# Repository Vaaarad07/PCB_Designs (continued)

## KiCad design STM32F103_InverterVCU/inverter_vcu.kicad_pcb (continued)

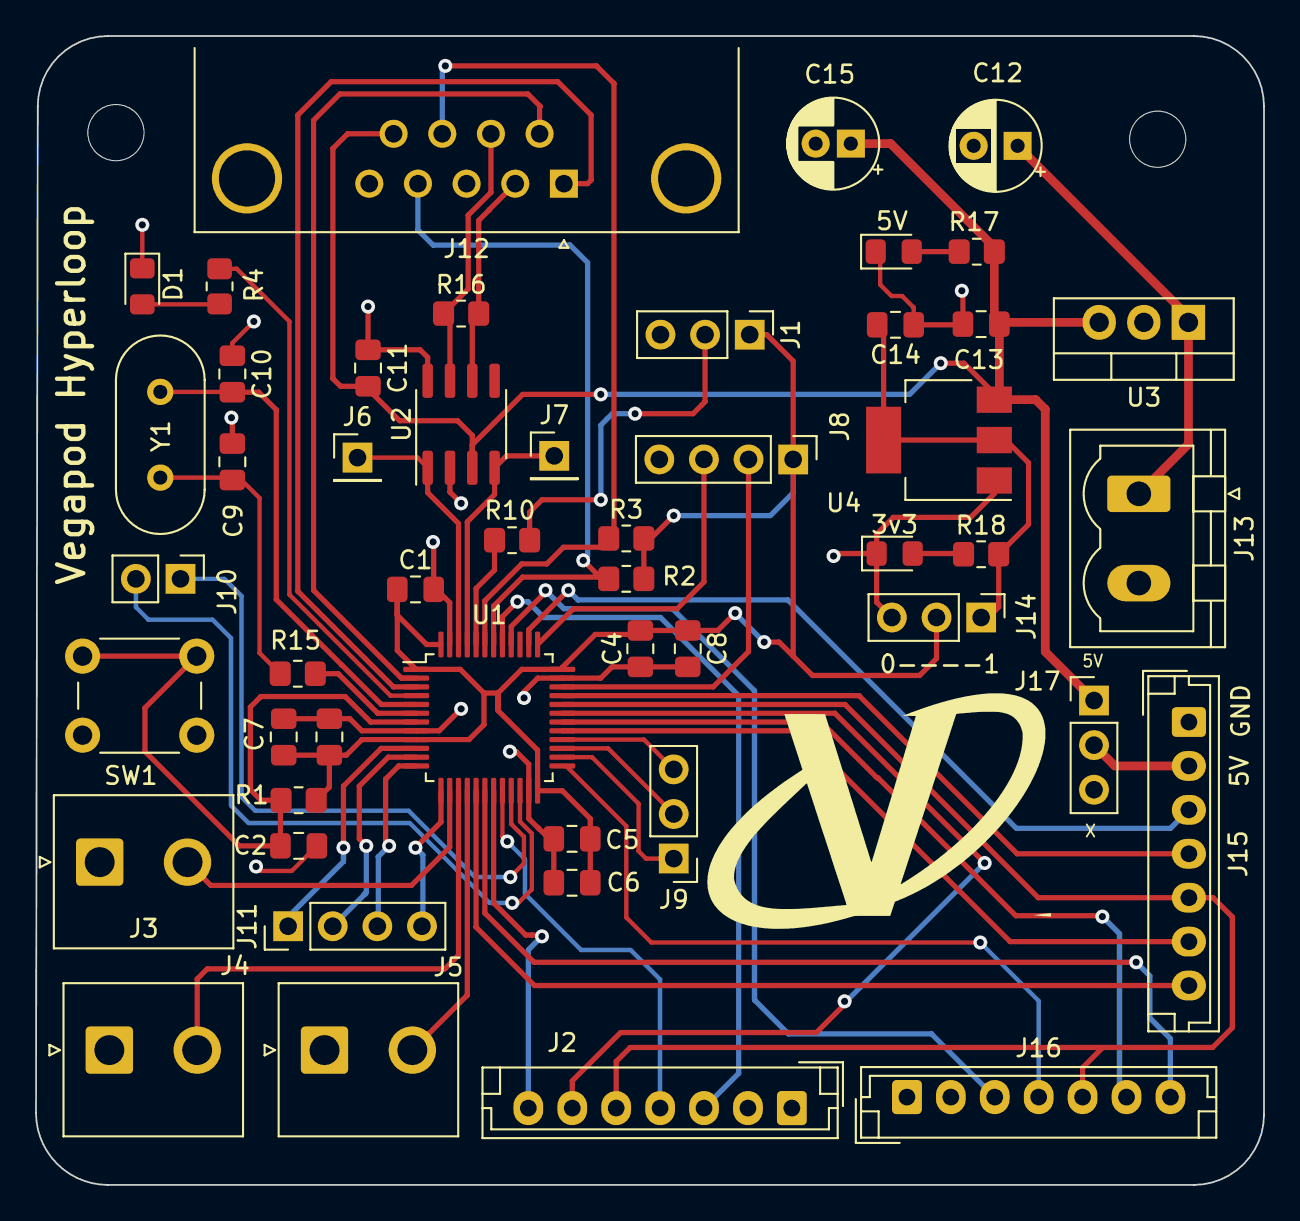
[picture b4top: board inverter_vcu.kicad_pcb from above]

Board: 2 copper layers, 69.9 x 65.4 mm, 50 parts (0 on the bottom side), 51 nets.

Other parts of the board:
3v3, 5V: LED; LED_0805_2012Metric_Pad1.15x1.40mm_HandSolder

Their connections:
GND: 3v3.1 (K), 5V.1 (K); also elsewhere on the board
unnamed 47: 5V.2 (A); also elsewhere on the board
unnamed 48: 3v3.2 (A); also elsewhere on the board

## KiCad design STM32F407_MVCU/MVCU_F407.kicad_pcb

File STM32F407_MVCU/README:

This folder contains KiCad PCB files for a custom Board.

This is a 4 layer STM32F407VGT6 custom board used as a MVCU in a vehicle control application.
The board connects to 5 separate Vehicle control units through DB9 connectors over the CAN bus. 
Following are some of the features of the board -
	Main input range 9-36 volts. Two power regulators to have two separate buses of 5V and 3.3V respectively.
	5 DB9 ports for VCU connections over CAN bus along with reserved gpios.
	RF transceiver (Xbee S2C pro)
	7 segment display
	DB9 port for IMU (Pollux 2) with RS232 to serial converter 
	SD Card slot
	10 User LEDs 
	5-pin Debugger/programmer connector
	Current monitoring
	UART, SPI, ADC, DAC, I2C connections

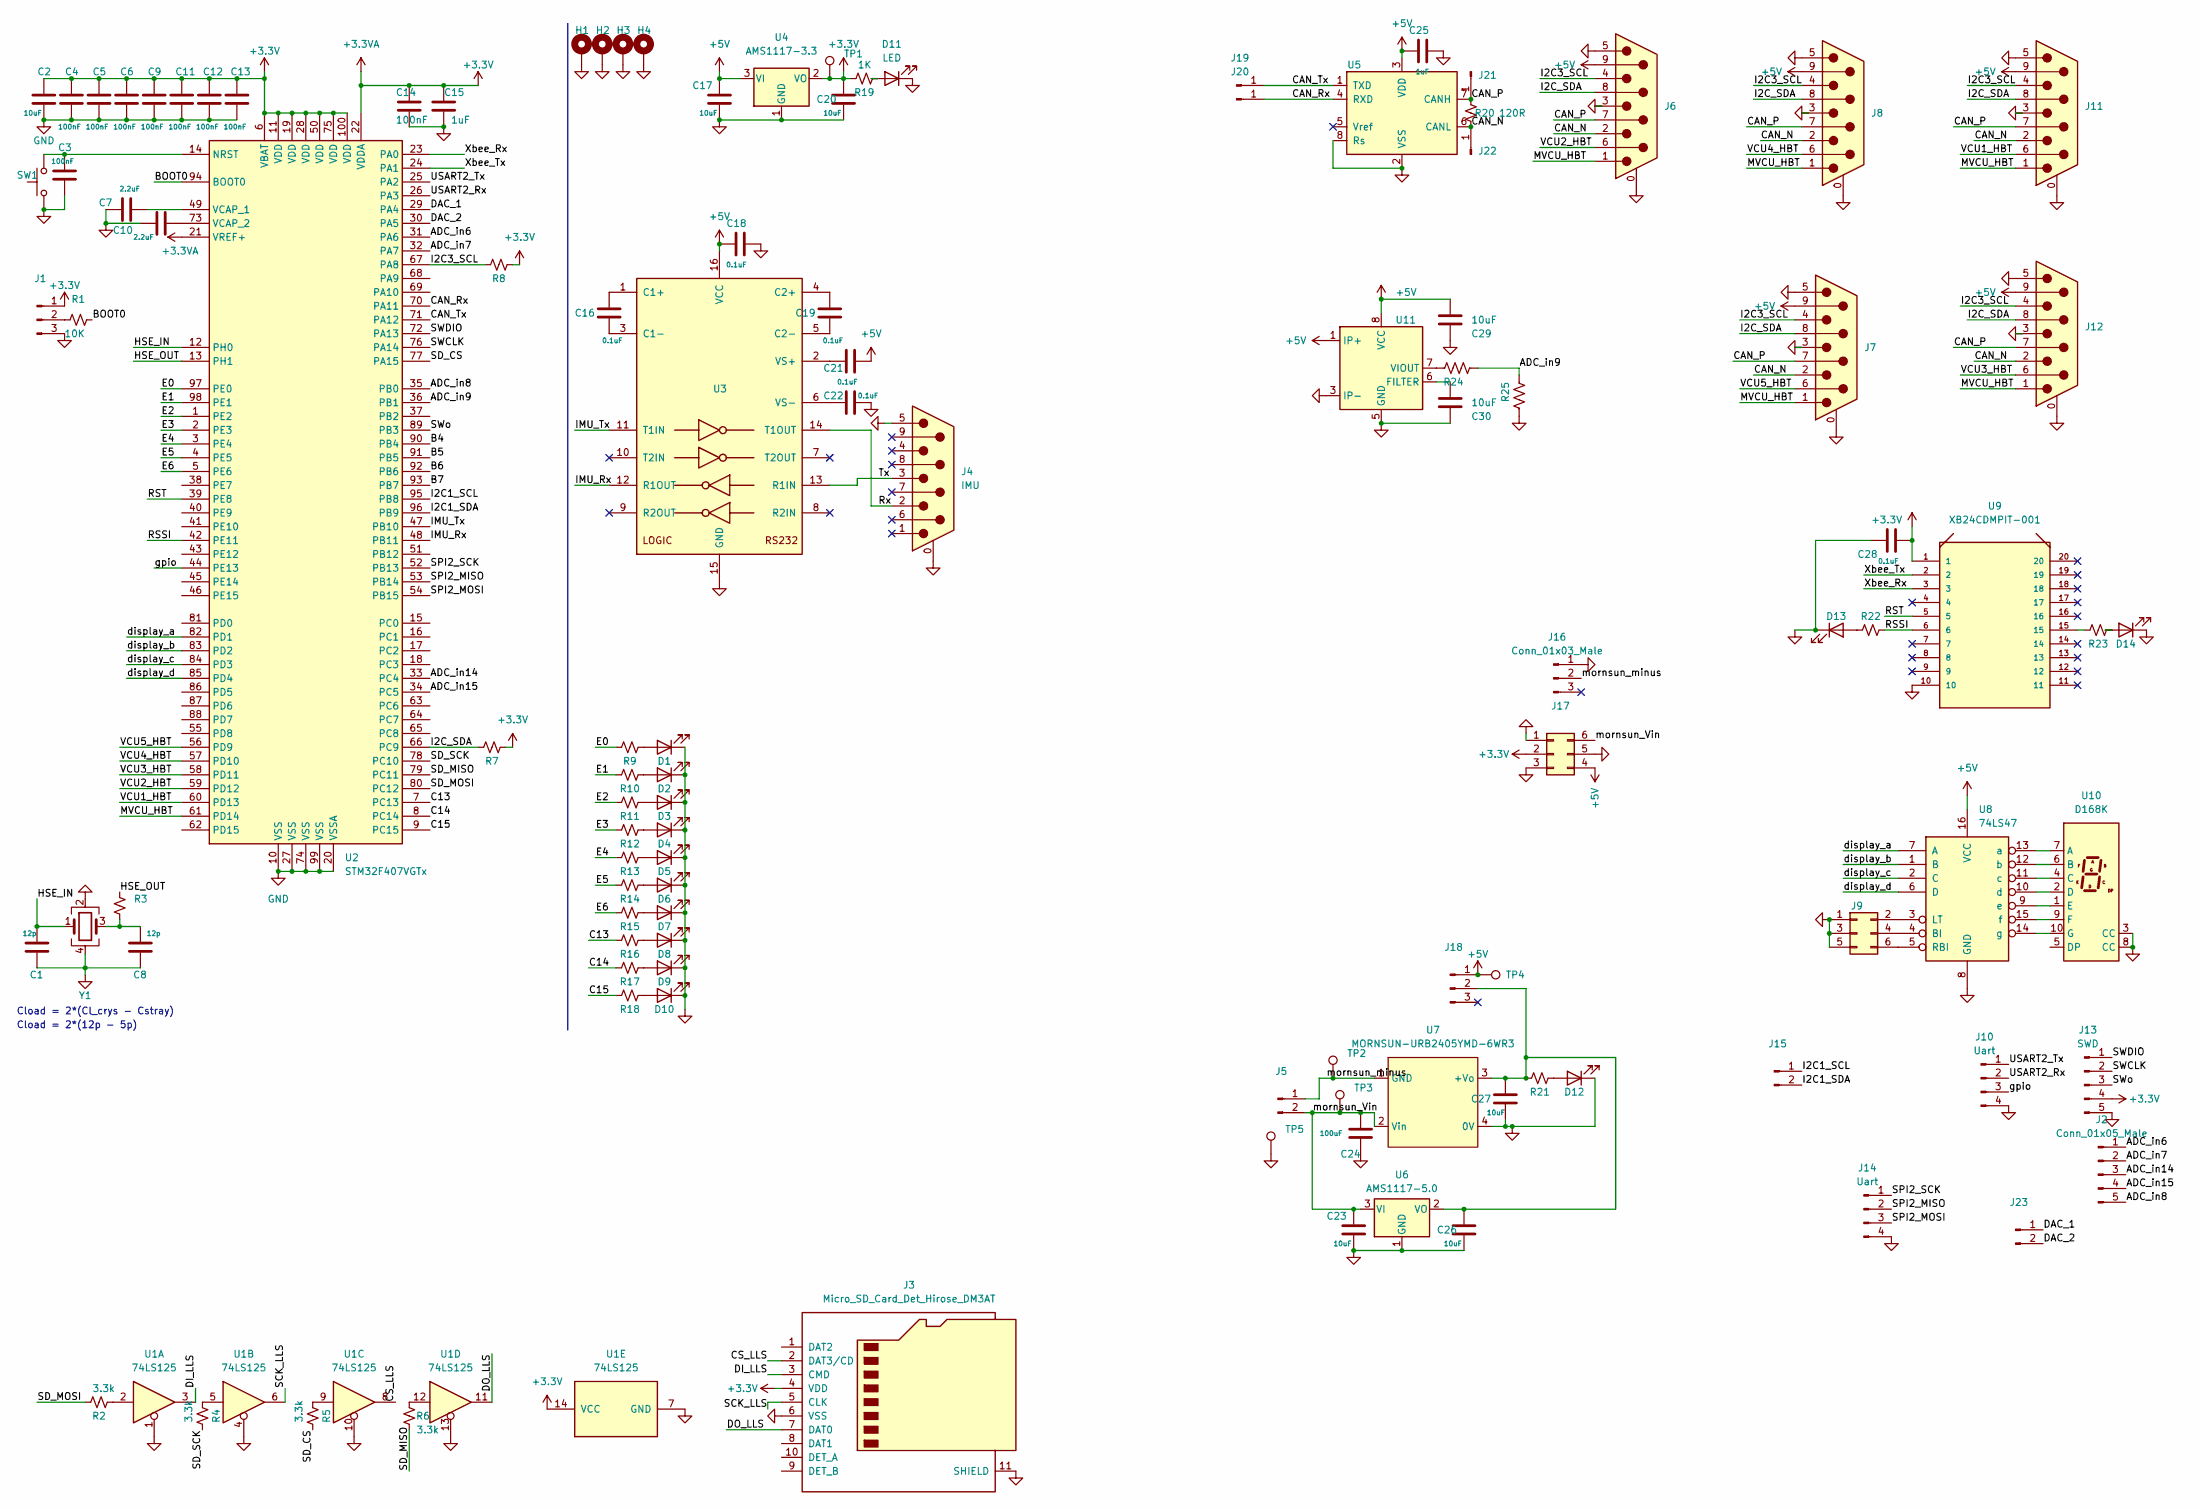
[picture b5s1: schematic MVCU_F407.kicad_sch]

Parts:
C1, C8: 12p; C_0805_2012Metric_Pad1.18x1.45mm_HandSolder
C2, C17, C20, C23, C26, C27, C29, C30: 10uF; C_0805_2012Metric_Pad1.18x1.45mm_HandSolder
C3, C4, C5, C6, C9, C11, C12, C13, C14: 100nF; C_0805_2012Metric_Pad1.18x1.45mm_HandSolder
C7, C10: 2.2uF; C_0805_2012Metric_Pad1.18x1.45mm_HandSolder
C15, C25: 1uF; C_0805_2012Metric_Pad1.18x1.45mm_HandSolder
C16, C18, C19, C21, C22, C28: 0.1uF; C_0805_2012Metric_Pad1.18x1.45mm_HandSolder
C24: 100uF; C_0805_2012Metric_Pad1.18x1.45mm_HandSolder
D1, D2, D3, D4, D5, D6, D7, D8, D9, D10, D11, D12, D13, D14: LED; LED_0805_2012Metric_Pad1.15x1.40mm_HandSolder
H1, H2, H3, H4: MountingHole_Pad; MountingHole_3.2mm_M3_DIN965_Pad
J1, J16, J18: Conn_01x03_Male; PinHeader_1x03_P2.54mm_Vertical
J2: Conn_01x05_Male; PinHeader_1x05_P2.54mm_Vertical
J3: Micro_SD_Card_Det_Hirose_DM3AT; microSD_HC_Hirose_DM3AT-SF-PEJM5
J4: IMU; DSUB-9_Male_Horizontal_P2.77x2.84mm_EdgePinOffset7.70mm_Hou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
J5: Conn_01x02_Male; PhoenixContact_MSTBA_2,5_2-G-5,08_1x02_P5.08mm_Horizontal
J6, J7, J8, J11, J12: DB9_Male_MountingHoles; DSUB-9_Male_Horizontal_P2.77x2.84mm_EdgePinOffset7.70mm_Hou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
J9: Conn_02x03_Odd_Even; PinSocket_1x06_P2.54mm_Vertical
J10, J14: Uart; PinHeader_1x04_P2.54mm_Vertical
J13: SWD; PinSocket_1x05_P2.54mm_Vertical
J15, J23: Conn_01x02_Male; PinHeader_1x02_P2.54mm_Vertical
J17: Conn_02x03_Counter_Clockwise; PinHeader_2x03_P2.54mm_Vertical
J19, J20, J21, J22: Conn_01x01_Male; PinHeader_1x01_P2.54mm_Vertical
R1: 10K; R_0805_2012Metric_Pad1.20x1.40mm_HandSolder
R2, R4, R5, R6: 3.3k; R_0805_2012Metric_Pad1.20x1.40mm_HandSolder
R3: R_Small_US; R_0805_2012Metric_Pad1.20x1.40mm_HandSolder
R7, R8, R9, R10, R11, R12, R13, R14, R15, R16, R17, R18, R19, R21, R22, R23: 1K; R_0805_2012Metric_Pad1.20x1.40mm_HandSolder
R20: 120R; R_0805_2012Metric_Pad1.20x1.40mm_HandSolder
R24, R25: 1.5k; R_0805_2012Metric_Pad1.20x1.40mm_HandSolder
SW1: SW_Push; SW_PUSH_6mm_H5mm
TP1, TP2, TP3, TP4, TP5: TestPoint; TestPoint_Keystone_5010-5014_Multipurpose
U1: 74LS125; DIP-14_W7.62mm
U2: STM32F407VGTx; LQFP-100_14x14mm_P0.5mm
U3: MAX232; DIP-16_W7.62mm_SMDSocket_SmallPads
U4: AMS1117-3.3; SOT-223-3_TabPin2
U5: MCP2551-I-SN; SOIC-8_3.9x4.9mm_P1.27mm
U6: AMS1117-5.0; SOT-223-3_TabPin2
U7: MORNSUN-URB2405YMD-6WR3
U8: 74LS47; DIP-16_W7.62mm
U9: XB24CDMPIT-001; XBEE
U10: D168K; D1X8K
U11: ACS712xLCTR-20A; SOIC-8_3.9x4.9mm_P1.27mm
Y1: Crystal_GND24; Crystal_SMD_3225-4Pin_3.2x2.5mm_HandSoldering

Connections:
+3.3V: C2.1, C4.1, C5.1, C6.1, C9.1, C11.1, C12.1, C13.1, C14.1, C15.1, C20.1, C28.1, J1.1, J3.4 (VDD), J13.4, J17.2, R7.1, R8.1, R19.2, TP1.1, U1.14 (VCC), U2.6 (VBAT), U2.11 (VDD), U2.19 (VDD), U2.21 (VREF+), U2.22 (VDDA), U2.28 (VDD), U2.50 (VDD), U2.75 (VDD), U2.100 (VDD), U4.2 (VO), U9.1; also elsewhere on the board
+5V: C17.1, C18.1, C21.1, C25.1, C29.1, J6.9, J7.9, J8.9, J11.9, J12.9, J17.4, J18.1, TP4.1, U3.16 (VCC), U4.3 (VI), U5.3 (VDD), U8.16 (VCC), U11.1 (IP+), U11.2 (IP+), U11.8 (VCC); also elsewhere on the board
/ADC_in6: J2.1, U2.31 (PA6)
/ADC_in7: J2.2, U2.32 (PA7)
/ADC_in8: J2.5, U2.35 (PB0)
/ADC_in9: R24.2, R25.1, U2.36 (PB1)
/ADC_in14: J2.3, U2.33 (PC4)
/ADC_in15: J2.4, U2.34 (PC5)
/B4: U2.90 (PB4)
/B5: U2.91 (PB5)
/B6: U2.92 (PB6)
/B7: U2.93 (PB7)
/BOOT0: R1.2, U2.94 (BOOT0)
/C13: R16.2, U2.7 (PC13)
/C14: R17.2, U2.8 (PC14)
/C15: R18.2, U2.9 (PC15)
/CAN_N: J6.2, J7.2, J8.2, J11.2, J12.2, J22.1, R20.2, U5.6 (CANL)
/CAN_P: J6.7, J7.7, J8.7, J11.7, J12.7, J21.1, R20.1, U5.7 (CANH)
/CAN_Rx: J20.1, U2.70 (PA11), U5.4 (RXD)
/CAN_Tx: J19.1, U2.71 (PA12), U5.1 (TXD)
/CS_LLS: J3.2 (DAT3/CD), U1.8
/DAC_1: J23.1, U2.29 (PA4)
/DAC_2: J23.2, U2.30 (PA5)
/DI_LLS: J3.3 (CMD), U1.3
/E0: R9.2, U2.97 (PE0)
/E1: R10.2, U2.98 (PE1)
/E2: R11.2, U2.1 (PE2)
/E3: R12.2, U2.2 (PE3)
/E4: R13.2, U2.3 (PE4)
/E5: R14.2, U2.4 (PE5)
/E6: R15.2, U2.5 (PE6)
/HSE_IN: C1.2, U2.12 (PH0), Y1.1
/HSE_OUT: R3.1, U2.13 (PH1)
/I2C1_SCL: J15.1, U2.95 (PB8)
/I2C1_SDA: J15.2, U2.96 (PB9)
/I2C3_SCL: J6.4, J7.4, J8.4, J11.4, J12.4, R8.2, U2.67 (PA8)
/I2C_SDA: J6.8, J7.8, J8.8, J11.8, J12.8, R7.2, U2.66 (PC9)
/IMU_Rx: U2.48 (PB11), U3.12 (R1OUT)
/IMU_Tx: U2.47 (PB10), U3.11 (T1IN)
/MVCU_HBT: J6.1, J7.1, J8.1, J11.1, J12.1, U2.61 (PD14)
/RSSI: R22.2, U2.42 (PE11), U9.6
/RST: U2.39 (PE8), U9.5
/Rx: J4.2, U3.14 (T1OUT)
/SCK_LLS: J3.5 (CLK), U1.6
/SD_CS: R5.2, U2.77 (PA15)
/SD_MOSI: R2.2, U2.80 (PC12)
/SD_SCK: R4.2, U2.78 (PC10)
/SPI2_MISO: J14.2, U2.53 (PB14)
/SPI2_MOSI: J14.3, U2.54 (PB15)
/SPI2_SCK: J14.1, U2.52 (PB13)
/SWCLK: J13.2, U2.76 (PA14)
/SWDIO: J13.1, U2.72 (PA13)
/SWo: J13.3, U2.89 (PB3)
/Tx: J4.3, U3.13 (R1IN)
/USART2_Rx: J10.2, U2.26 (PA3)
/USART2_Tx: J10.1, U2.25 (PA2)
/VCU1_HBT: J11.6, U2.60 (PD13)
/VCU2_HBT: J6.6, U2.59 (PD12)
/VCU3_HBT: J12.6, U2.58 (PD11)
/VCU4_HBT: J8.6, U2.57 (PD10)
/VCU5_HBT: J7.6, U2.56 (PD9)
/Xbee_Rx: U2.23 (PA0), U9.3
/Xbee_Tx: U2.24 (PA1), U9.2
/display_a: U2.82 (PD1), U8.7 (A)
/display_b: U2.83 (PD2), U8.1 (B)
/display_c: U2.84 (PD3), U8.2 (C)
/display_d: U2.85 (PD4), U8.6 (D)
/gpio: J10.3, U2.44 (PE13)
/mornsun_Vin: C23.1, C24.1, J5.2, J17.6, TP3.1, U6.3 (VI), U7.2 (Vin); also elsewhere on the board
/mornsun_minus: J5.1, J16.2, TP2.1, U7.1 (GND); also elsewhere on the board
GND: C1.1, C2.2, C3.2, C4.2, C5.2, C6.2, C7.1, C8.1, C9.2, C10.1, C11.2, C12.2, C13.2, C14.2, C15.2, C17.2, C18.2, C20.2, C22.1, C23.2, C24.2, C25.2, C26.2, C27.1, C28.2, C29.2, C30.2, D1.1 (K), D2.1 (K), D3.1 (K), D4.1 (K), D5.1 (K), D6.1 (K), D7.1 (K), D8.1 (K), D9.1 (K), D10.1 (K), D11.1 (K), D12.1 (K), D13.1 (K), D14.1 (K), H1.1, H2.1, H3.1, H4.1, J1.3, J3.6 (VSS), J3.11 (SHIELD), J4.0 (PAD), J4.5, J6.0 (PAD), J6.3, J6.5, J7.0 (PAD), J7.3, J7.5, J8.0 (PAD), J8.3, J8.5, J9.1, J9.3, J9.5, J10.4, J11.0 (PAD), J11.3, J11.5, J12.0 (PAD), J12.3, J12.5, J13.5, J14.4, J16.1, J17.1, J17.3, J17.5, R25.2, SW1.1, TP5.1, U1.1, U1.4, U1.7 (GND), U1.10, U1.13, U2.10 (VSS), U2.20 (VSSA), U2.27 (VSS), U2.74 (VSS), U2.99 (VSS), U3.15 (GND), U4.1 (GND), U5.2 (VSS), U5.8 (Rs), U6.1 (GND), U7.4 (0V), U8.8 (GND), U9.10, U10.3 (CC), U10.8 (CC), U11.3 (IP-), U11.4 (IP-), U11.5 (GND), Y1.2, Y1.4; also elsewhere on the board
unnamed: C3.1, SW1.2, U2.14 (NRST)
unnamed: C7.2, U2.49 (VCAP_1)
unnamed: C8.2, R3.2, Y1.3
unnamed: C10.2, U2.73 (VCAP_2)
unnamed: C16.1, U3.3 (C1-)
unnamed: C16.2, U3.1 (C1+)
unnamed: C19.1, U3.5 (C2-)
unnamed: C19.2, U3.4 (C2+)
unnamed: C21.2, U3.2 (VS+)
unnamed: C22.2, U3.6 (VS-)
unnamed: C26.1, C27.2, J18.2, R21.2, U6.2 (VO), U7.3 (+Vo)
unnamed: C30.1, U11.6 (FILTER)
unnamed: D1.2 (A), R9.1
unnamed: D2.2 (A), R10.1
unnamed: D3.2 (A), R11.1
unnamed: D4.2 (A), R12.1
unnamed: D5.2 (A), R13.1
unnamed: D6.2 (A), R14.1
unnamed: D7.2 (A), R15.1
unnamed: D8.2 (A), R16.1
unnamed: D9.2 (A), R17.1
unnamed: D10.2 (A), R18.1
unnamed: D11.2 (A), R19.1
unnamed: D12.2 (A), R21.1
unnamed: D13.2 (A), R22.1
unnamed: D14.2 (A), R23.1
unnamed: J1.2, R1.1
unnamed: J9.2, U8.3 (LT)
unnamed: J9.4, U8.4 (BI)
unnamed: J9.6, U8.5 (RBI)
unnamed: R2.1, U1.2
unnamed: R4.1, U1.5
unnamed: R5.1, U1.9
unnamed: R6.1, U1.12
unnamed: R23.2, U9.15
unnamed: R24.1, U11.7 (VIOUT)
unnamed: U8.9 (e), U10.1 (E)
unnamed: U8.10 (d), U10.2 (D)
unnamed: U8.11 (c), U10.4 (C)
unnamed: U8.12 (b), U10.6 (B)
unnamed: U8.13 (a), U10.7 (A)
unnamed: U8.15 (f), U10.9 (F)
unnamed: U8.14 (g), U10.10 (G)

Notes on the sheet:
Cload = 2*(12p - 5p)
Cload = 2*(Cl_crys - Cstray)

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
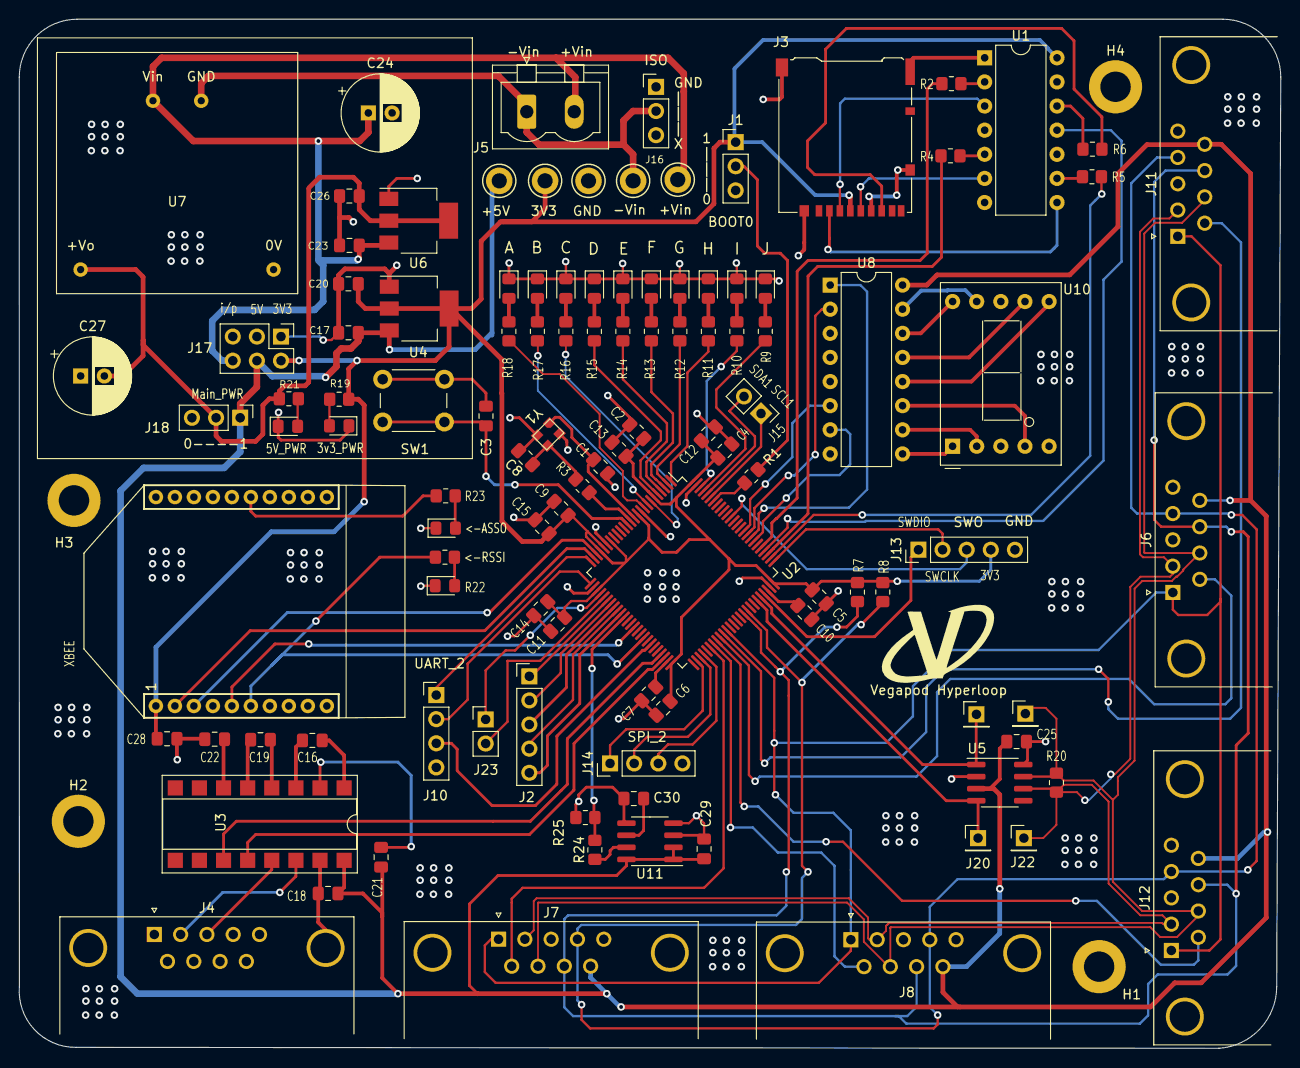
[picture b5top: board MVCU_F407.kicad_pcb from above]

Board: 4 copper layers, 132.8 x 108.4 mm, 113 parts (0 on the bottom side), 109 nets.

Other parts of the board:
3V3: TestPoint; TestPoint_Keystone_5010-5014_Multipurpose
+5V: TestPoint; TestPoint_Keystone_5010-5014_Multipurpose
+Vin: TestPoint; TestPoint_Keystone_5010-5014_Multipurpose
-Vin: TestPoint; TestPoint_Keystone_5010-5014_Multipurpose
GND: TestPoint; TestPoint_Keystone_5010-5014_Multipurpose

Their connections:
+3.3V: 3V3.1; also elsewhere on the board
+5V: +5V.1; also elsewhere on the board
/mornsun_Vin: +Vin.1; also elsewhere on the board
/mornsun_minus: -Vin.1; also elsewhere on the board
GND: GND.1; also elsewhere on the board

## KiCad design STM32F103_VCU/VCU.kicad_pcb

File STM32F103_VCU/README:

This folder contains KiCad PCB files for a custom Board.

This is a 2 layer STM32F103C8T6 custom board used as a VCU in a vehicle control application.
The board connects to a Master Vehicle control unit a through DB9 connector over the CAN bus. 
Following are some of the features of the board -
	 Powered through the MVCU (Master board) or from power input (7-36V)
	 Separate 5V and 3.3V buses
	 CAN bus
	 5 User LEDs
	 Current monitoring
	 4-pin debugger/programmer connector
	 UART, SPI, I2C, ADC ports

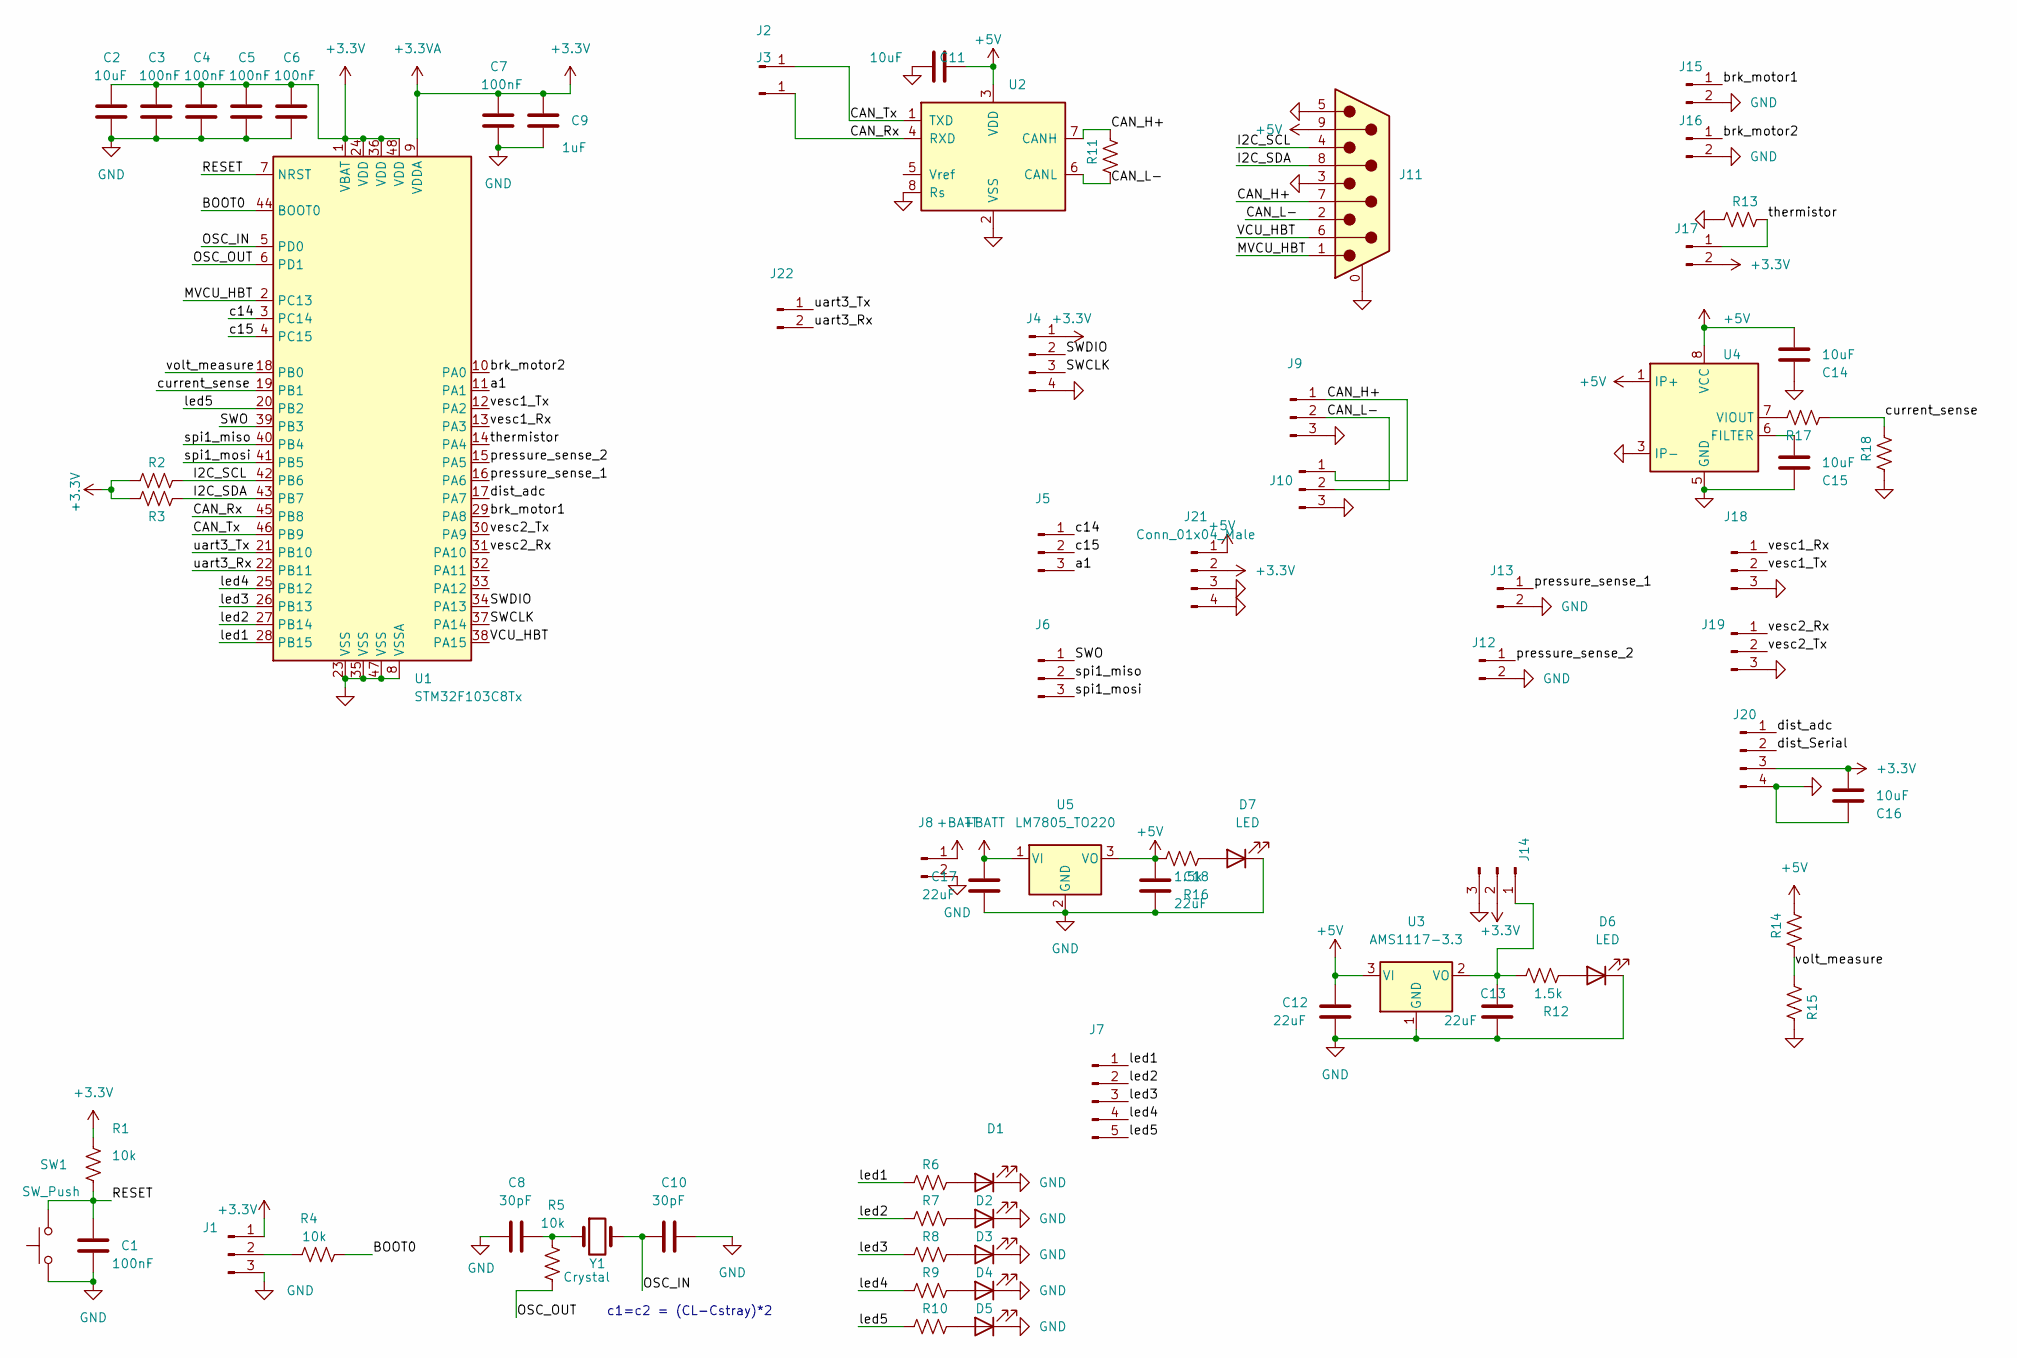
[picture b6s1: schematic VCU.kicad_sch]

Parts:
C1, C3, C4, C5, C6, C7: 100nF; C_0805_2012Metric_Pad1.18x1.45mm_HandSolder
C2, C11, C14, C15, C16: 10uF; C_0805_2012Metric_Pad1.18x1.45mm_HandSolder
C8, C10: 30pF; C_0805_2012Metric_Pad1.18x1.45mm_HandSolder
C9: 1uF; C_0805_2012Metric_Pad1.18x1.45mm_HandSolder
C12, C13, C17, C18: 22uF; C_0805_2012Metric_Pad1.18x1.45mm_HandSolder
D1, D2, D3, D4, D5, D6, D7: LED; LED_0805_2012Metric_Pad1.15x1.40mm_HandSolder
J1, J5, J6, J14: Conn_01x03_Male; PinHeader_1x03_P2.54mm_Vertical
J2, J3: Conn_01x01_Male; PinHeader_1x01_P2.54mm_Vertical
J4: Conn_01x04_Male; PinHeader_1x04_P2.54mm_Vertical
J7: Conn_01x05_Male; PinHeader_1x05_P2.54mm_Vertical
J8: Conn_01x02_Male; PhoenixContact_MSTBVA_2,5_2-G-5,08_1x02_P5.08mm_Vertical
J9, J10: Conn_01x03_Male; JST_EH_B3B-EH-A_1x03_P2.50mm_Vertical
J11: DB9_Male_MountingHoles; DSUB-9_Male_Horizontal_P2.77x2.84mm_EdgePinOffset4.94mm_Hou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
J12, J13, J15, J16, J17: Conn_01x02_Male; JST_NV_B02P-NV_1x02_P5.00mm_Vertical
J18, J19: Conn_01x03_Male; JST_NV_B03P-NV_1x03_P5.00mm_Vertical
J20, J21: Conn_01x04_Male; JST_NV_B04P-NV_1x04_P5.00mm_Vertical
J22: Conn_01x02_Male; PinHeader_1x02_P2.54mm_Vertical
R1, R4, R5: 10k; R_0805_2012Metric_Pad1.20x1.40mm_HandSolder
R2, R3, R6, R7, R8, R9, R10, R11, R12, R13, R14, R15, R16, R17, R18: 1.5k; R_0805_2012Metric_Pad1.20x1.40mm_HandSolder
SW1: SW_Push; SW_PUSH_6mm_H5mm
U1: STM32F103C8Tx; LQFP-48_7x7mm_P0.5mm
U2: MCP2551-I-SN; SOIC-8_3.9x4.9mm_P1.27mm
U3: AMS1117-3.3; SOT-223-3_TabPin2
U4: ACS712xLCTR-20A; SOIC-8_3.9x4.9mm_P1.27mm
U5: LM7805_TO220; TO-220-3_Vertical
Y1: Crystal; Crystal_HC49-U_Vertical

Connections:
+3.3V: C2.1, C3.1, C4.1, C5.1, C6.1, C7.1, C9.1, C16.1, J1.1, J4.1, J14.2, J17.2, J20.3, J21.2, R1.1, R2.2, R3.2, U1.1 (VBAT), U1.9 (VDDA), U1.24 (VDD), U1.36 (VDD), U1.48 (VDD)
+5V: C11.2, C12.1, C14.1, C18.1, J11.9, J21.1, R14.1, R16.2, U2.3 (VDD), U3.3 (VI), U4.1 (IP+), U4.2 (IP+), U4.8 (VCC), U5.3 (VO)
+BATT: C17.1, J8.1, U5.1 (VI)
/BOOT0: R4.2, U1.44 (BOOT0)
/CAN_H+: J9.1, J10.1, J11.7, R11.1, U2.7 (CANH)
/CAN_L-: J9.2, J10.2, J11.2, R11.2, U2.6 (CANL)
/CAN_Rx: J3.1, U1.45 (PB8), U2.4 (RXD)
/CAN_Tx: J2.1, U1.46 (PB9), U2.1 (TXD)
/I2C_SCL: J11.4, R2.1, U1.42 (PB6)
/I2C_SDA: J11.8, R3.1, U1.43 (PB7)
/MVCU_HBT: J11.1, U1.2 (PC13)
/OSC_IN: C10.2, U1.5 (PD0), Y1.2
/OSC_OUT: R5.1, U1.6 (PD1)
/RESET: C1.1, R1.2, SW1.2, U1.7 (NRST)
/SWCLK: J4.3, U1.37 (PA14)
/SWDIO: J4.2, U1.34 (PA13)
/SWO: J6.1, U1.39 (PB3)
/VCU_HBT: J11.6, U1.38 (PA15)
/a1: J5.3, U1.11 (PA1)
/brk_motor1: J15.1, U1.29 (PA8)
/brk_motor2: J16.1, U1.10 (PA0)
/c14: J5.1, U1.3 (PC14)
/c15: J5.2, U1.4 (PC15)
/current_sense: R17.2, R18.1, U1.19 (PB1)
/dist_Serial: J20.2
/dist_adc: J20.1, U1.17 (PA7)
/led1: J7.1, R6.2, U1.28 (PB15)
/led2: J7.2, R7.2, U1.27 (PB14)
/led3: J7.3, R8.2, U1.26 (PB13)
/led4: J7.4, R9.2, U1.25 (PB12)
/led5: J7.5, R10.2, U1.20 (PB2)
/pressure_sense_1: J13.1, U1.16 (PA6)
/pressure_sense_2: J12.1, U1.15 (PA5)
/spi1_miso: J6.2, U1.40 (PB4)
/spi1_mosi: J6.3, U1.41 (PB5)
/thermistor: J17.1, R13.1, U1.14 (PA4)
/uart3_Rx: J22.2, U1.22 (PB11)
/uart3_Tx: J22.1, U1.21 (PB10)
/vesc1_Rx: J18.1, U1.13 (PA3)
/vesc1_Tx: J18.2, U1.12 (PA2)
/vesc2_Rx: J19.1, U1.31 (PA10)
/vesc2_Tx: J19.2, U1.30 (PA9)
/volt_measure: R14.2, R15.2, U1.18 (PB0)
GND: C1.2, C2.2, C3.2, C4.2, C5.2, C6.2, C7.2, C8.2, C9.2, C10.1, C11.1, C12.2, C13.2, C14.2, C15.2, C16.2, C17.2, C18.2, D1.1 (K), D2.1 (K), D3.1 (K), D4.1 (K), D5.1 (K), D6.1 (K), D7.1 (K), J1.3, J4.4, J8.2, J9.3, J10.3, J11.0 (PAD), J11.3, J11.5, J12.2, J13.2, J14.3, J15.2, J16.2, J18.3, J19.3, J20.4, J21.3, J21.4, R13.2, R15.1, R18.2, SW1.1, U1.8 (VSSA), U1.23 (VSS), U1.35 (VSS), U1.47 (VSS), U2.2 (VSS), U2.8 (Rs), U3.1 (GND), U4.3 (IP-), U4.4 (IP-), U4.5 (GND), U5.2 (GND); also elsewhere on the board
unnamed: C8.1, R5.2, Y1.1
unnamed: C13.1, J14.1, R12.2, U3.2 (VO)
unnamed: C15.1, U4.6 (FILTER)
unnamed: D1.2 (A), R6.1
unnamed: D2.2 (A), R7.1
unnamed: D3.2 (A), R8.1
unnamed: D4.2 (A), R9.1
unnamed: D5.2 (A), R10.1
unnamed 52: D6.2 (A), R12.1; also elsewhere on the board
unnamed 53: D7.2 (A), R16.1; also elsewhere on the board
unnamed: J1.2, R4.1
unnamed: R17.1, U4.7 (VIOUT)

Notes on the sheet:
c1=c2 = (CL-Cstray)*2

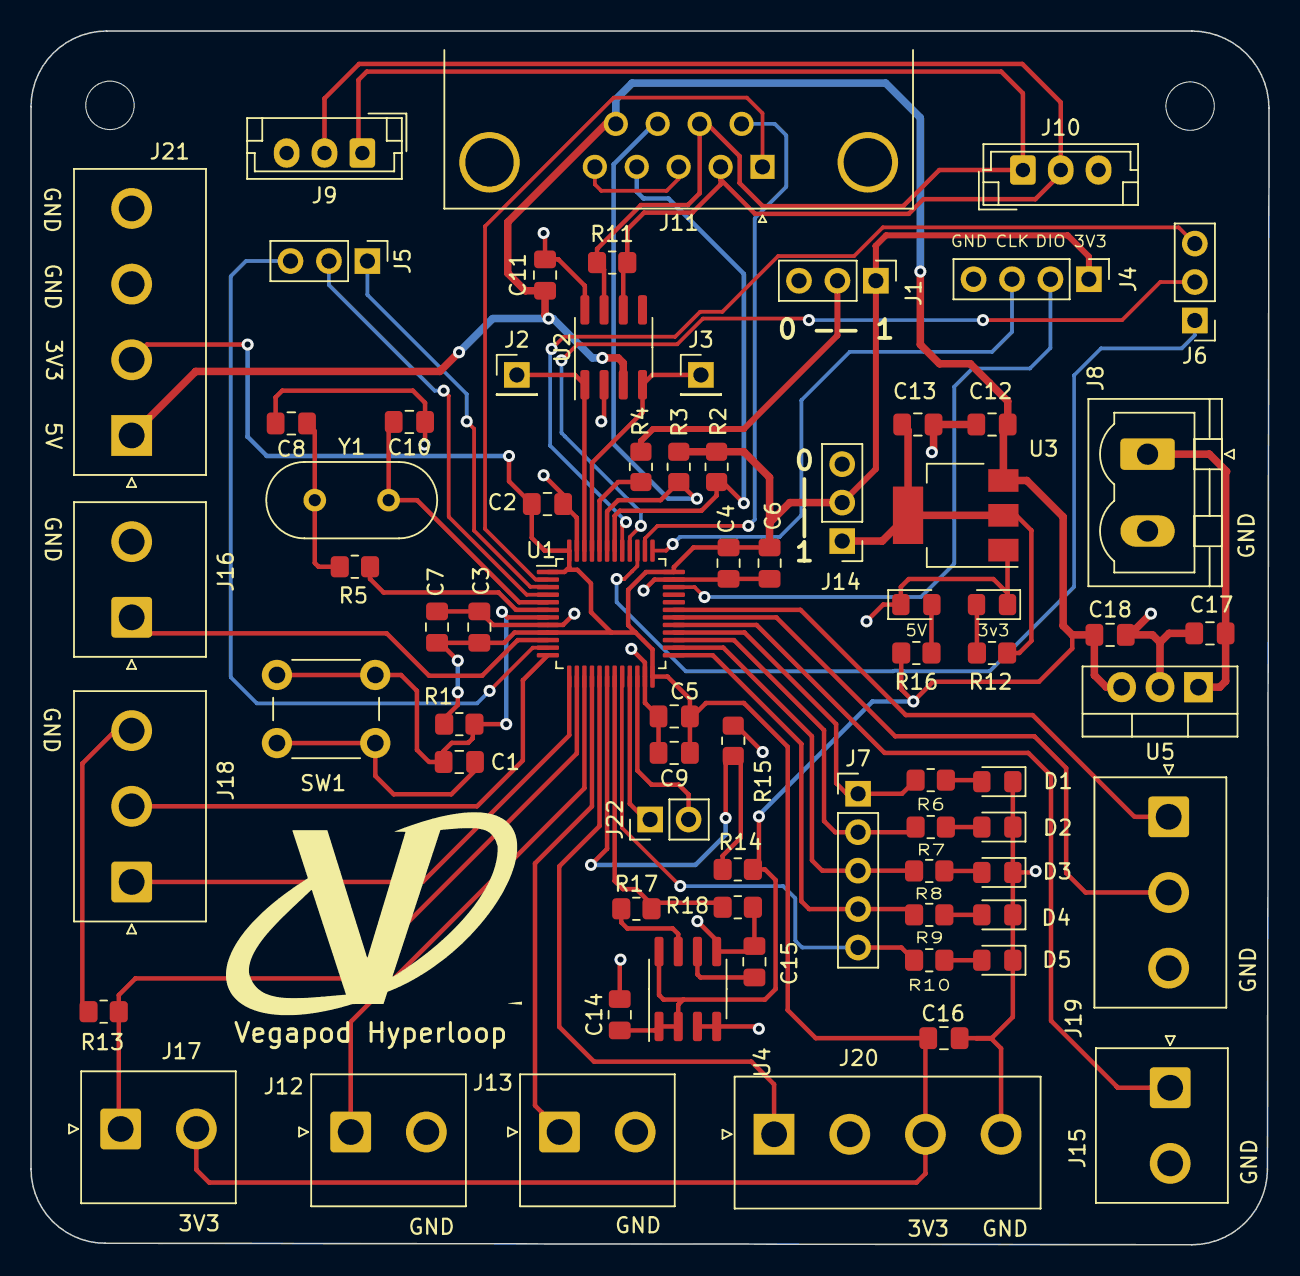
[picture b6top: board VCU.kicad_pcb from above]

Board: 2 copper layers, 81.8 x 80.2 mm, 72 parts (0 on the bottom side), 55 nets.

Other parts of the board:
3v3, 5V: LED; LED_0805_2012Metric_Pad1.15x1.40mm_HandSolder

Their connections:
GND: 3v3.1 (K), 5V.1 (K); also elsewhere on the board
unnamed 52: 3v3.2 (A); also elsewhere on the board
unnamed 53: 5V.2 (A); also elsewhere on the board

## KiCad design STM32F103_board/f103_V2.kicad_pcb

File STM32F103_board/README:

This folder contains KiCad PCB files for a custom Board.

This is a 2 layer STM32F103C8T6 custom test board.
T 
Following are some of the features of the board -
	 Powered through the DB9 port (Master board) or from power input (7-36V) or USB.
	 Separate 5V and 3.3V buses
	 CAN bus
	 7-segment display
	 4-pin debugger/programmer connector
	 UART, SPI, I2C, ADC ports

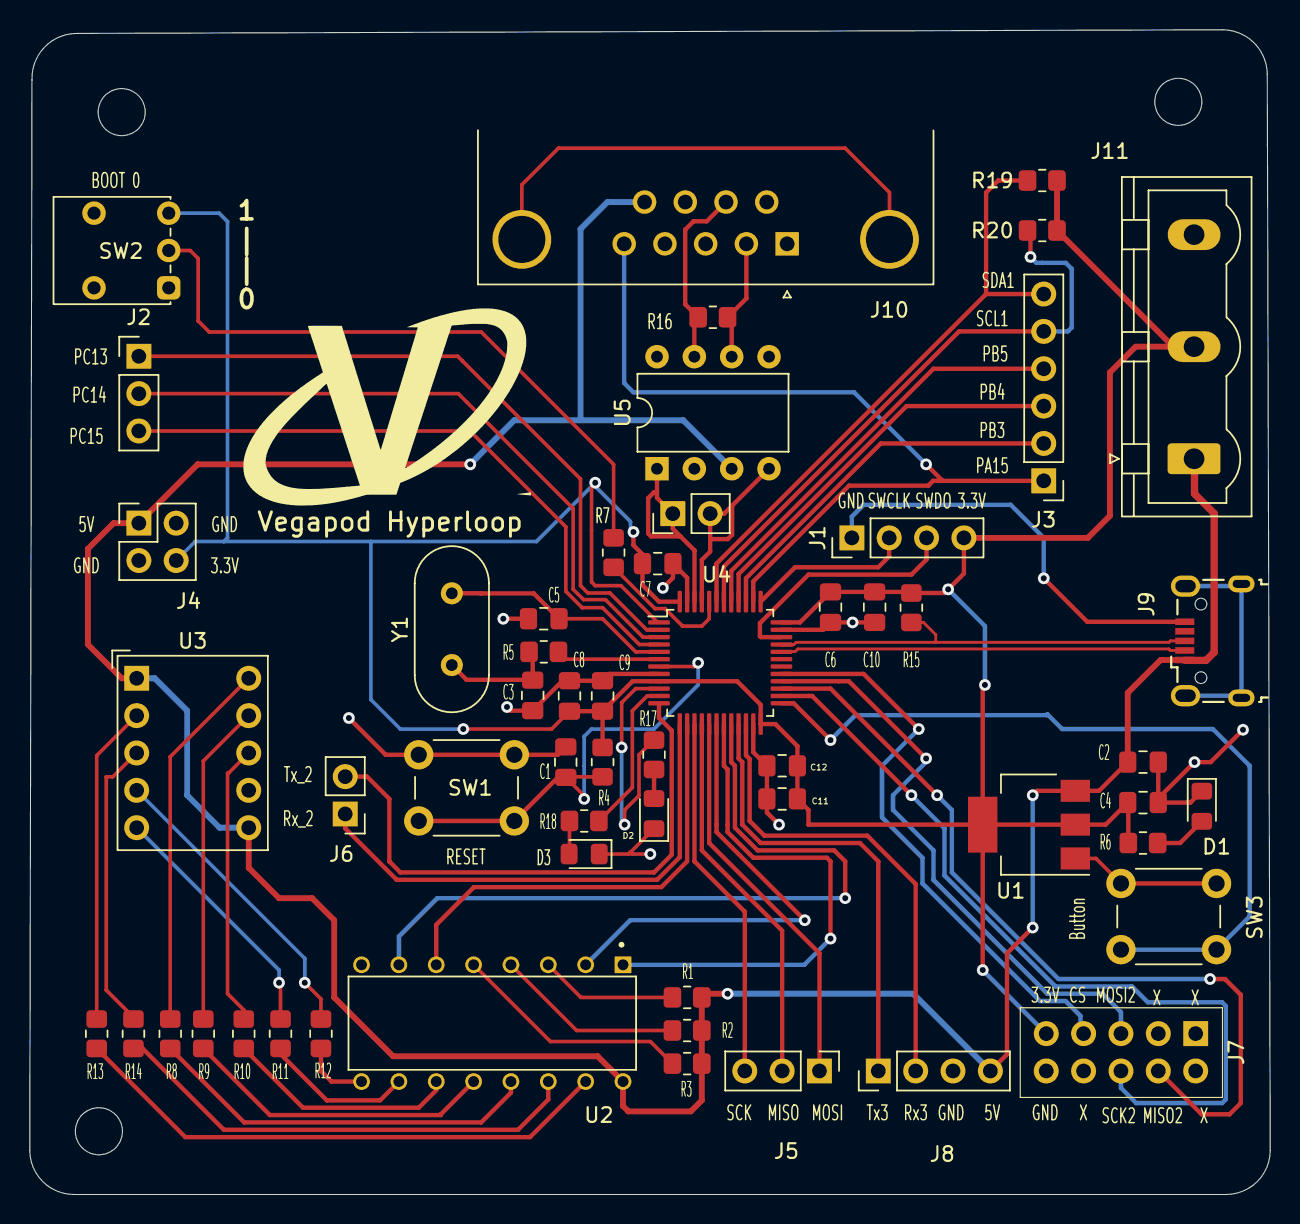
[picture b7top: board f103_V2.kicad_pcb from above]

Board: 2 copper layers, 84.4 x 79.2 mm, 56 parts (1 on the bottom side), 64 nets.

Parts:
C1, C6, C7, C8, C9, C10, C11: 100nF; C_0805_2012Metric_Pad1.18x1.45mm_HandSolder
C2, C4: 22uF; C_0805_2012Metric_Pad1.18x1.45mm_HandSolder
C3, C5: 30pF; C_0805_2012Metric_Pad1.18x1.45mm_HandSolder
C12: 1uF; C_0805_2012Metric_Pad1.18x1.45mm_HandSolder
D1, D2, D3: LED; LED_0805_2012Metric_Pad1.15x1.40mm_HandSolder
J1, J8: Conn_01x04_Male; PinHeader_1x04_P2.54mm_Vertical
J2, J5: Conn_01x03_Male; PinHeader_1x03_P2.54mm_Vertical
J3: Conn_01x06_Male; PinHeader_1x06_P2.54mm_Vertical
J4: Conn_02x02_Odd_Even; PinHeader_2x02_P2.54mm_Vertical
J6, J12: Conn_01x02_Male; PinHeader_1x02_P2.54mm_Vertical
J7: Conn_02x05_Top_Bottom; PinSocket_2x05_P2.54mm_Vertical
J9: USB_B_Micro; USB_Micro-B_Wuerth_629105150521
J10: DB9_Male_MountingHoles; DSUB-9_Male_Horizontal_P2.77x2.84mm_EdgePinOffset4.94mm_Hou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
J11: Conn_01x03_Male; PhoenixContact_GMSTBVA_2,5_3-G-7,62_1x03_P7.62mm_Vertical
R1, R2, R3, R8, R9, R10, R11, R12, R13, R14, R19, R20: R_US; R_0805_2012Metric_Pad1.20x1.40mm_HandSolder
R4, R5, R7: 10k; R_0805_2012Metric_Pad1.20x1.40mm_HandSolder
R6, R15, R17, R18: 1.5k; R_0805_2012Metric_Pad1.20x1.40mm_HandSolder
R16: 120; R_0805_2012Metric_Pad1.20x1.40mm_HandSolder
SW1, SW3: SW_Push; SW_PUSH_6mm_H5mm
SW2: SW_SPDT; SW_Push_1P2T_Vertical_E-Switch_800UDP8P1A1M6
U1: AMS1117-3.3; SOT-223-3_TabPin2
U2: 74LS47; DIP794W45P254L1930H508Q16
U3: SA39-12EWA; Sx39-1xxxxx
U4: STM32F103C8Tx; LQFP-48_7x7mm_P0.5mm
U5: MCP2551-I-SN; DIP-8_W7.62mm
Y1: Crystal; Crystal_HC49-U_Vertical

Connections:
+3.3V: C4.1, C6.1, C7.1, C8.1, C9.1, C10.1, C11.1, C12.1, J1.4, J4.4, J7.9, J11.2, R4.1, R6.2, R15.2, R19.2, R20.2, SW2.3 (C), U1.2 (VO), U4.1 (VBAT), U4.9 (VDDA), U4.24 (VDD), U4.36 (VDD), U4.48 (VDD)
/BOOT0: R7.2, U4.44 (BOOT0)
/CAN_Rx: J12.2, U4.45 (PB8), U5.4 (RXD)
/CAN_Tx: J12.1, U4.46 (PB9), U5.1 (TXD)
/CS: J7.7, U4.29 (PA8)
/Display_A: U2.7 (A), U4.20 (PB2)
/Display_B: U2.1 (B), U4.19 (PB1)
/Display_C: U2.2 (C), U4.18 (PB0)
/Display_D: U2.6 (D), U4.14 (PA4)
/I2C_1_SCL: J3.5, R20.1, U4.42 (PB6)
/I2C_1_SDA: J3.6, R19.1, U4.43 (PB7)
/LED1: R17.2, U4.10 (PA0)
/LED2: R18.2, U4.11 (PA1)
/OSC_IN: C5.2, U4.5 (PD0), Y1.2
/OSC_OUT: R5.1, U4.6 (PD1)
/PA15: J3.1, J10.5, U4.38 (PA15)
/PB4: J3.3, U4.40 (PB4)
/PB5: J3.4, U4.41 (PB5)
/PC13: J2.1, U4.2 (PC13)
/PC14: J2.2, U4.3 (PC14)
/PC15: J2.3, U4.4 (PC15)
/RESET: C1.1, R4.2, SW1.2, U4.7 (NRST)
/SPI_1_MISO: J5.2, U4.16 (PA6)
/SPI_1_MOSI: J5.1, U4.17 (PA7)
/SPI_1_SCK: J5.3, U4.15 (PA5)
/SPI_2_MISO: J7.4, U4.27 (PB14)
/SPI_2_MOSI: J7.5, U4.28 (PB15)
/SPI_2_SCK: J7.6, U4.26 (PB13)
/SW_DIO: J1.3, U4.34 (PA13)
/SW_SCK: J1.2, U4.37 (PA14)
/SW_Trace: J3.2, U4.39 (PB3)
/UART_2_Rx: J6.1, U4.13 (PA3)
/UART_2_Tx: J6.2, U4.12 (PA2)
/UART_3_Rx: J8.2, U4.22 (PB11)
/UART_3_Tx: J8.1, U4.21 (PB10)
/USB_D+: J9.3 (D+), R15.1, U4.33 (PA12)
/USB_D-: J9.2 (D-), U4.32 (PA11)
/Usr_Push_btn: SW3.2, U4.25 (PB12)
GND: C1.2, C2.2, C3.2, C4.2, C5.1, C6.2, C7.2, C8.2, C9.2, C10.2, C11.2, C12.2, D1.1 (K), D2.1 (K), D3.1 (K), J1.1, J4.2, J4.3, J7.10, J8.3, J9.5 (GND), J10.3, J10.6, J11.3, SW1.1, SW2.1 (A), SW3.1, U1.1 (GND), U2.8 (GND), U4.8 (VSSA), U4.23 (VSS), U4.35 (VSS), U4.47 (VSS), U5.2 (VSS), U5.8 (Rs)
unnamed: C3.1, R5.2, Y1.1
unnamed: D1.2 (A), R6.1
unnamed: D2.2 (A), R17.1
unnamed: D3.2 (A), R18.1
unnamed: J10.2, R16.1, U5.6 (CANL)
unnamed: J10.7, R16.2, U5.7 (CANH)
unnamed: R1.2, U2.3 (LT)
unnamed: R2.2, U2.4 (BI)
unnamed: R3.2, U2.5 (RBI)
unnamed: R7.1, SW2.2 (B)
unnamed: R8.1, U2.13 (a)
unnamed: R8.2, U3.10 (A)
unnamed: R9.1, U2.12 (b)
unnamed: R9.2, U3.9 (B)
unnamed: R10.1, U2.11 (c)
unnamed: R10.2, U3.8 (C)
unnamed: R11.1, U2.10 (d)
unnamed: R11.2, U3.5 (D)
unnamed: R12.1, U2.9 (e)
unnamed: R12.2, U3.4 (E)
unnamed: R13.1, U2.15 (f)
unnamed: R13.2, U3.2 (F)
unnamed: R14.1, U2.14 (g)
unnamed: R14.2, U3.3 (G)
VBUS: C2.1, J4.1, J8.4, J9.1 (VBUS), J10.9, J11.1, R1.1, R2.1, R3.1, U1.3 (VI), U2.16 (VCC), U3.1 (CA), U3.6 (CA), U5.3 (VDD)
